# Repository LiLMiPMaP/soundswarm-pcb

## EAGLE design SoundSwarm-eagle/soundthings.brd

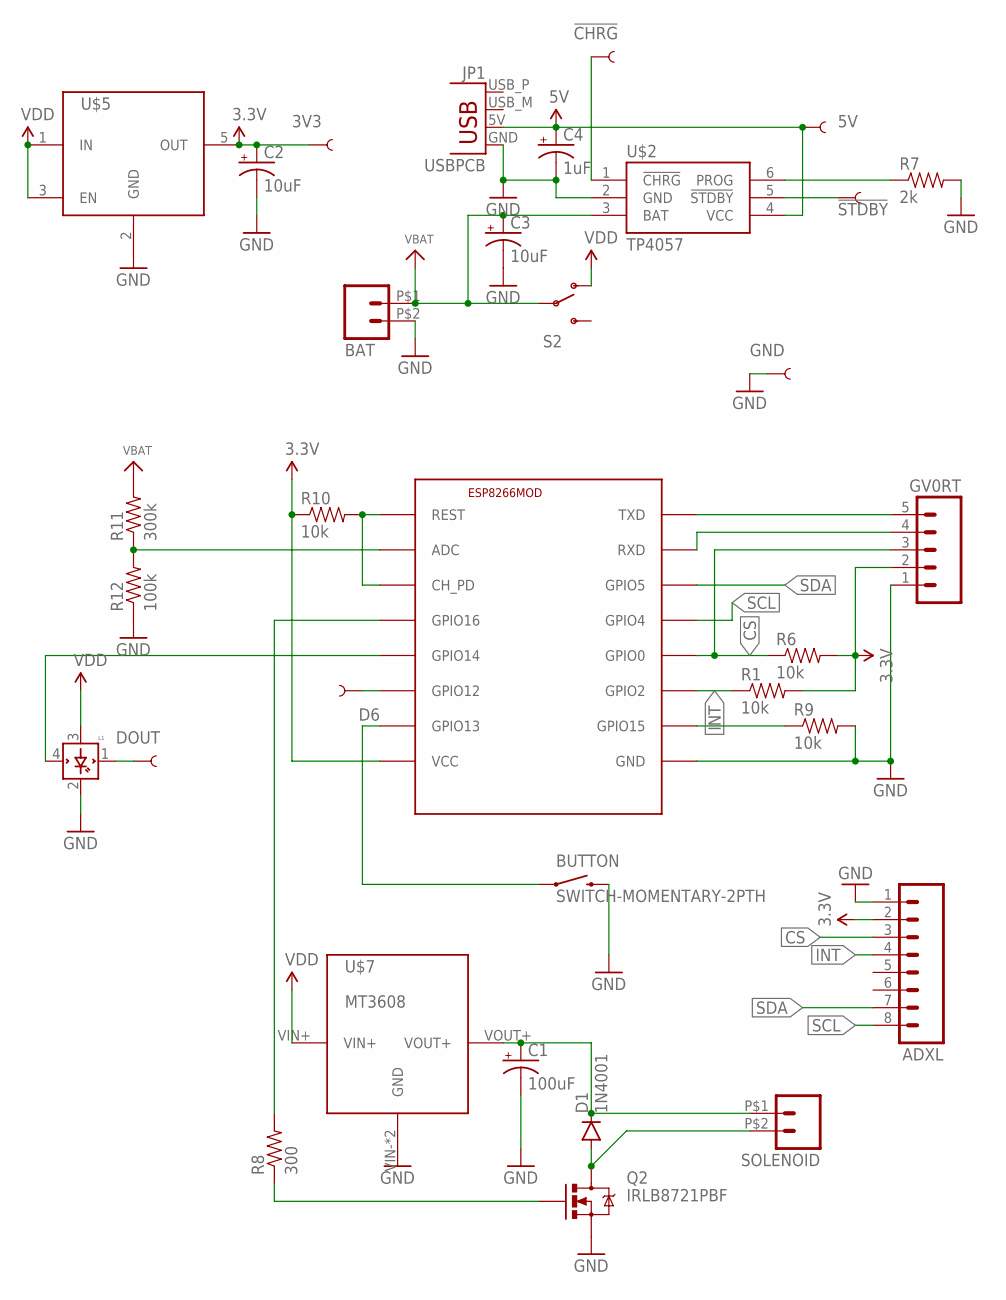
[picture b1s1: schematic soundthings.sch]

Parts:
3V3, 5V: TEST-POINTTP_15TH_THRU; TP_15TH
!CHRG: TEST-POINTTP_15TH_THRU; TP_15TH
!STDBY: TEST-POINTTP_15TH_THRU; TP_15TH
ADXL: M08LOCK; 1X08_LOCK
BAT: M02PTH2; 1X02_BIG
BUTTON: SWITCH-MOMENTARY-2PTH; TACTILE-PTH
C1: 100uF; CPOL-RADIAL-100UF-25V
C2, C3: 10uF; CPOL-RADIAL-100UF-25V
C4: 1uF; CPOL-RADIAL-100UF-25V
D1: 1N4001; DIODE-1N4148
D6: TEST-POINTTP_15TH_THRU; TP_15TH
DOUT: TEST-POINTTP_15TH_THRU; TP_15TH
ESP8266MOD: ESP8266-07; ESP-07
GND: TEST-POINTTP_15TH_THRU; TP_15TH
GV0RT: M05LOCK; 1X05_LOCK
JP1: USBPCB; USB-A-PCB
L1: WS2812BTH; WS2812F5
Q2: IRLB8721PBF; TO220V
R1, R6, R9, R10: 10k; AXIAL-0.3
R7: 2k; AXIAL-0.3
R8: 300; AXIAL-0.3
R11: 300k; AXIAL-0.3
R12: 100k; AXIAL-0.3
S2: SWITCH-SPDT-1; MHS122-1
SOLENOID: M02PTH2; 1X02_BIG
U$2: TP4057; SOT23-6
U$5: TLV70233; SOT23-5
U$7: MT3608

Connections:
3.3V: 3V3.P$1, ADXL.2, C2.1 (+), ESP8266MOD.VCC, GV0RT.2, R1.P$2 (2), R6.P$2 (2), R10.P$1 (1), U$5.5 (OUT)
5V: 5V.P$1, C4.1 (+), JP1.5V (VBUS), U$2.4 (VCC)
!CHRG: !CHRG.P$1, U$2.1 (!CHRG)
!STDBY: !STDBY.P$1, U$2.5 (!STDBY)
ADC: ESP8266MOD.ADC, R11.P$1 (1), R12.P$2 (2)
CS: ADXL.3, ESP8266MOD.GPIO0, GV0RT.3, R6.P$1 (1)
DOUT: DOUT.P$1, L1.1 (DOUT)
EN: ESP8266MOD.CH_PD, ESP8266MOD.REST, R10.P$2 (2)
GATE: Q2.1 (G), R8.P$1 (1)
GND: ADXL.1, BAT.P$2 (2), BUTTON.3 (2), C1.2 (-), C2.2 (-), C3.2 (-), C4.2 (-), ESP8266MOD.GND, GND.P$1, GV0RT.1, JP1.GND, L1.2 (GND), Q2.3 (S), R7.P$2 (2), R9.P$2 (2), R12.P$1 (1), U$2.2 (GND), U$5.2 (GND), U$7.VIN- (GND), U$7.VOUT- (GND)
GPIO12: D6.P$1, ESP8266MOD.GPIO12
GPIO13: BUTTON.1, ESP8266MOD.GPIO13
GPIO14: ESP8266MOD.GPIO14, L1.4 (DIN)
GPIO15: ESP8266MOD.GPIO15, R9.P$1 (1)
GPIO16: ESP8266MOD.GPIO16, R8.P$2 (2)
INT: ADXL.4, ESP8266MOD.GPIO2, R1.P$1 (1)
unnamed: R7.P$1 (1), U$2.6 (PROG)
RX: ESP8266MOD.RXD, GV0RT.4
SCL: ADXL.8, ESP8266MOD.GPIO5 (GPIO4)
SDA: ADXL.7, ESP8266MOD.GPIO4 (GPIO5)
SOL-: D1.A, Q2.2 (D), SOLENOID.P$2 (2)
TX: ESP8266MOD.TXD, GV0RT.5
VOUT+: C1.1 (+), D1.C, SOLENOID.P$1 (1), U$7.VOUT+

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
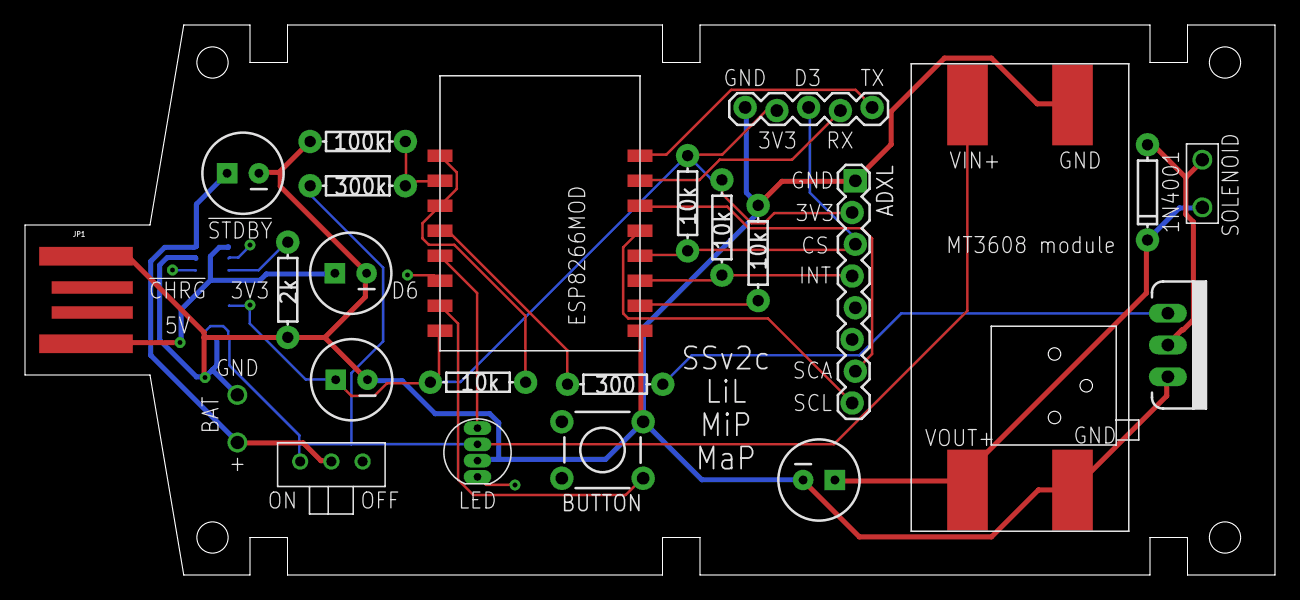
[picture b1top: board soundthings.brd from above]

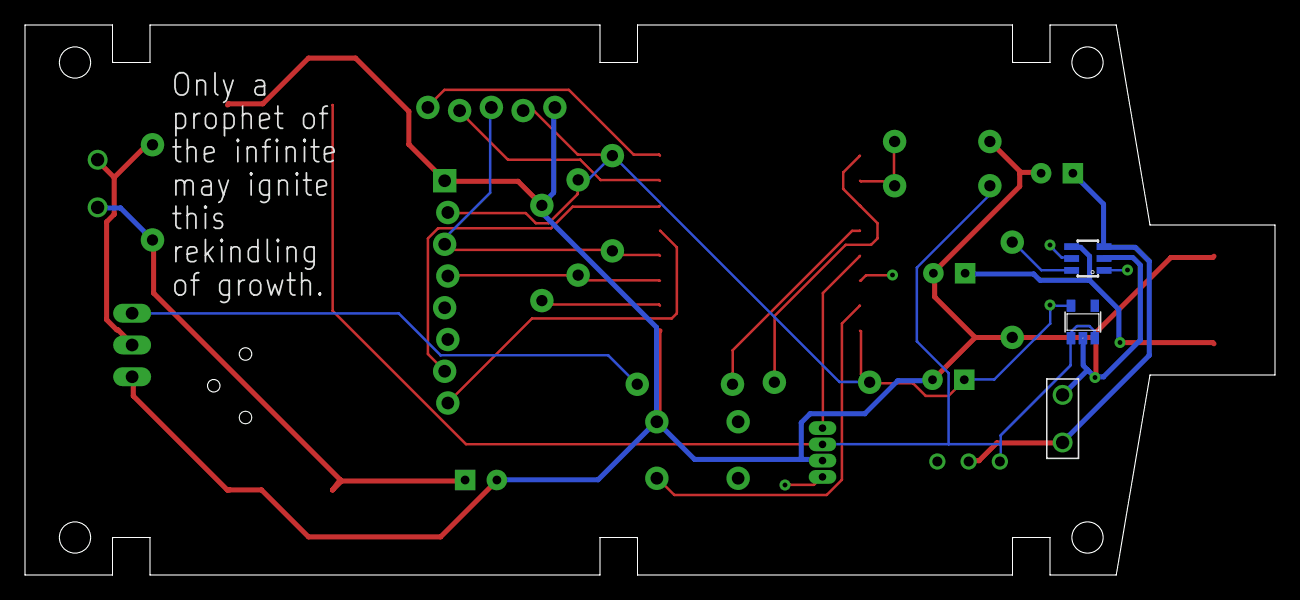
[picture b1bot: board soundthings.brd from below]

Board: 2 copper layers, 100.0 x 44.0 mm, 33 parts (3 on the bottom side), 25 nets.

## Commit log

2017-02-13 Initial PCB as ordered
2017-03-01 v1 GERBER files as ordered
2017-03-01 v2 (to be tested)
2017-03-04 Update board with mounting holes
2017-03-11 changed shape of board and moved components close to usb interface further in
2017-03-12 removed names and added values
2017-03-15 New schematic using DC-DC converter; needs Eagle-Lio-Library
2017-03-16 Fixed PCB layout v2
2017-03-16 case for friction fit solenoid and strap hooks
2017-03-16 same as yesterday, added pin-locking for solenoid
2017-03-16 ERC and DRC passed; rotated wifi
2017-03-18 Move away from the edges; add labels
2017-03-18 added vectors of latest board
2017-03-18 As submitted to ditrypcbs
2017-03-18 Fixed: DC-DC on VDD (switched)
2017-03-19 Add CC-BY-SA-4.0 license
2017-03-19 SSv2c with fixed VDD battery measurement
2017-03-19 pcb added as vector
2017-03-19 changed file structure of vectors

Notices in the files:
parts and their libraries:
SparkFun-Capacitors: Licensing: Creative Commons ShareAlike 4.0 International - https://creativecommons.org/licenses/by-sa/4.0
microbuilder: This work is placed in the public domain, and may be freely used for commercial and non-commercial work with the following conditions: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
